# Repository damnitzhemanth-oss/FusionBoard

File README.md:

# Fusion Board

## 1. Project Overview

### What is Fusion Board ?

Fusion Board is an MPSoc (Multi-Processor System-on-Chip) built from scratch based on AMD Zynq Ultrascale + architecture.
This board features 4GB DDR4 RAM, 32GB Memory, E Ink Display and much more.
(*Note : Checkout Repo guide for repo navigation*)

### Goals and Objectives.

I designed this board to explore a new domain after making projects like [Flight controller](https://github.com/damnitzhemanth-oss/Flight_Controller/tree/main)
, [Calculator](https://github.com/damnitzhemanth-oss/Custom-Scientific-Calc).

### Key Features.

Zynq UltraScale+ XCZU4E,900-pin FBVB900 SoC with 4 GB DDR4 (4× MT40A512M16LY), 256 Mb QSPI, 32 GB eMMC, and microSD.
With High Speed connectivity Peripherals like SFP+ cage, PCIE, superspeed USB. There are 10 LDOs for different voltages such as +15V, +5V, +3V3, +2.5V, +1.8V, +0V9, +0V85.

On board barometer, GNSS, Gyro, magnetometer. With power harvester and a super capacitor for storing energy.

(*Note : There are many more amazing features, checkout [Features for Nerds](https://github.com/damnitzhemanth-oss/FusionBoard/blob/main/Guides/DetailsForNerds.md)
for detailed specs list.*)

---

## 2. Requirements

### Hardware Requirements 
(*Rough estimated prices according to LCSC, in $*)

| # | Reference | Qty | Value | LCSC Part | Subtotal (USD) |
|---:|:---|--:|:---|:---|--:|
| 1 | BT1 | 1 | Battery_Cell |  | 0.42 |
| 2 | C1,C3,C8 | 3 | 1uF |  | 0.02 |
| 3 | C2,C9,C15 | 3 | 100uF 35V |  | 0.33 |
| 4 | C4 | 1 | 100nF |  | 0.00 |
| 5 | C5,C10 | 2 | 1uF 25V |  | 0.01 |
| 6 | C6 | 1 | 2.2uF |  | 0.01 |
| 7 | C7,C26,C31,C412...C500 | 37 | 100nF |  | 0.10 |
| 8 | C11 | 1 | 0.1uF 50V X7R |  | 0.00 |
| 9 | C12,C13,C20 | 3 | 10nF 25V |  | 0.01 |
| 10 | C14,C81,C85,C111,C_shield1 | 5 | 4.7nF 50V |  | 0.01 |
| 11 | C16 | 1 | 2.2nF 25V |  | 0.00 |
| 12 | C17,C18,C66,C68,C70,C72,C74,C94,C105,C119 | 10 | 0.1uF 25V |  | 0.03 |
| 13 | C19,C21 | 2 | 0.1uF 50V |  | 0.01 |
| 14 | C22 | 1 | 47nF |  | 0.00 |
| 15 | C23,C24,C28,C29,C30,C50,C52,C60,C61,C64,C65 | 11 | 22uF |  | 0.31 |
| 16 | C25,C45,C48,C62,C101...C498 | 35 | 1uF |  | 0.10 |
| 17 | C27 | 1 | 4.7uF |  | 0.01 |
| 18 | C32,C33,C37 | 3 | 1uF |  | 0.02 |
| 19 | C34 | 1 | 0.47uF |  | 0.00 |
| 20 | C35,C39 | 2 | 10nF |  | 0.01 |
| 21 | C36,C58,C59,C63...C507 | 26 | 10uF |  | 0.29 |
| 22 | C38 | 1 | 0.1uF |  | 0.01 |
| 23 | C40 | 1 | 22uF, 6.3V |  | 0.03 |
| 24 | C41,C49 | 2 | 0.1uF, 25V |  | 0.01 |
| 25 | C42,C43,C82,C86,C103,C112,C477,C478,C495,C496 | 10 | 100pF |  | 0.03 |
| 26 | C44 | 1 | 10nF, 10V |  | 0.00 |
| 27 | C46,C79,C83,C109 | 4 | 10nF |  | 0.01 |
| 28 | C47 | 1 | 3.3nF |  | 0.00 |
| 29 | C51 | 1 | 2.2nF |  | 0.00 |
| 30 | C53,C54,C55,C56 | 4 | 47uF,4V |  | 0.22 |
| 31 | C57,C97,C99,C107,C113 | 5 | 47uF |  | 0.28 |
| 32 | C76,C78,C104 | 3 | 0.1uF 25v |  | 0.01 |
| 33 | C77,C121...C523 | 300 | 0.1uF |  | 0.83 |
| 34 | C80,C84,C91,C96,C110,C118 | 6 | 22uf 25v |  | 0.21 |
| 35 | C87,C88,C114,C481,C482 | 5 | 22pF |  | 0.01 |
| 36 | C89,C90,C92,C93,C115,C116 | 6 | 47uF 6.3V |  | 0.33 |
| 37 | C154,C174 | 2 | 47uF |  | 0.17 |
| 38 | C368,C369,C370,C380,C381,C382,C383,C392,C422 | 9 | 1nF |  | 0.03 |
| 39 | C372,C373,C408,C409 | 4 | 33pF |  | 0.01 |
| 40 | C375,C385 | 2 | 22uF |  | 0.03 |
| 41 | C424,C429,C431 | 3 | 10uF |  | 0.06 |
| 42 | C473 | 1 | 0.56 nF |  | 0.00 |
| 43 | C474 | 1 | 330 nF |  | 0.00 |
| 44 | C475 | 1 | 3.3 nF |  | 0.00 |
| 45 | C499 | 1 | 0.1 uF |  | 0.00 |
| 46 | C518 | 1 | 22F 5.5V |  | 1.11 |
| 47 | Card1 | 1 | TF-01A | C91145 | 0.17 |
| 48 | CN1 | 1 | 1-2199230-6 | C4710843 | 1.39 |
| 49 | D1 | 1 | SMBJ20A |  | 0.08 |
| 50 | D2 | 1 | 15V |  | 0.08 |
| 51 | D3 | 1 | TP7.OSMD24CA-XC |  | 0.11 |
| 52 | D4 | 1 | LSMB24CAH |  | 0.11 |
| 53 | D5 | 1 | Red |  | 0.01 |
| 54 | D6,D9 | 2 | Green |  | 0.03 |
| 55 | D7,D8 | 2 | D_Schottky |  | 0.14 |
| 56 | D10,D11,D12 | 3 | RB521S30 |  | 0.08 |
| 57 | DC1 | 1 | PJ-102AH_C3096093 | C3096093 | 0.60 |
| 58 | FB1,FB2,FB3,FB4,FB5,FB6,FB7,FB8,FB10 | 9 | 120Ω@100MHz |  | 0.06 |
| 59 | FB9 | 1 | BLM18 |  | 0.01 |
| 60 | J1 | 1 | HR911105A_C12074 | C12074 | 1.35 |
| 61 | J2 | 1 | Conn_01x03_Pin |  | 0.14 |
| 62 | J3 | 1 | USB3_B |  | 1.11 |
| 63 | J4,J5 | 2 | Conn_01x02_Pin |  | 0.22 |
| 64 | J6 | 1 | 3.3V_I2C |  | 0.11 |
| 65 | J7,J14,J15,J16 | 4 | Conn_01x10 |  | 0.83 |
| 66 | J8 | 1 | Conn_01x09_Pin |  | 0.19 |
| 67 | J9 | 1 | Conn_Coaxial |  | 1.39 |
| 68 | J10 | 1 | Conn_02x07_Odd_Even |  | 0.28 |
| 69 | J11 | 1 | Conn_01x04_Pin |  | 0.14 |
| 70 | J12 | 1 | SFP+ |  | 2.08 |
| 71 | J13 | 1 | Conn_01x22 |  | 1.11 |
| 72 | L1,L2 | 2 | 2.2uH,5A |  | 0.42 |
| 73 | L3 | 1 | 1/2.2uH |  | 0.21 |
| 74 | L4 | 1 | 0.47uH 15A |  | 0.28 |
| 75 | L5 | 1 | 10uH 12A |  | 0.28 |
| 76 | L6,L7 | 2 | 2.2uH |  | 0.42 |
| 77 | L8,L9,L10 | 3 | 1uH |  | 0.42 |
| 78 | L11 | 1 | DLW21HN900SQ2L-CUTTAPE | C80529 | 0.14 |
| 79 | L12,L13,L14 | 3 | 220 nH |  | 0.13 |
| 80 | Q1,Q2 | 2 | IPB180P04P4L-02 | C21547650 | 2.22 |
| 81 | R1,R3,R135,R138,R163,R164 | 6 | 5.1kΩ |  | 0.01 |
| 82 | R2,R13,R41,R49,R50,R52,R54,R56,R59,R153,R155,R165,R166 | 13 | 100kΩ |  | 0.02 |
| 83 | R4,R7,R20,R21,R22,R23,R24,R29,R75 | 9 | 10k |  | 0.01 |
| 84 | R5 | 1 | 100Ω |  | 0.00 |
| 85 | R6,R8,R177,R178,R181 | 5 | 4.7kΩ |  | 0.01 |
| 86 | R9,R25 | 2 | 124k |  | 0.00 |
| 87 | R10,R27,R34...R212 | 54 | 10kΩ |  | 0.08 |
| 88 | R11,R12,R60,R65,R70,R73,R74,R76,R78,R90,R101 | 11 | 100k |  | 0.02 |
| 89 | R14 | 1 | 549Ω |  | 0.00 |
| 90 | R15,R26 | 2 | 750Ω |  | 0.00 |
| 91 | R16,R17 | 2 | 470R |  | 0.00 |
| 92 | R18 | 1 | 29.8k |  | 0.00 |
| 93 | R19,R92 | 2 | 120k |  | 0.00 |
| 94 | R28 | 1 | 5.9kΩ |  | 0.00 |
| 95 | R30 | 1 | 442k |  | 0.00 |
| 96 | R31 | 1 | 210k |  | 0.00 |
| 97 | R32 | 1 | 20.5k |  | 0.00 |
| 98 | R33 | 1 | 10mΩ |  | 0.69 |
| 99 | R37,R48,R104,R105,R140,R145 | 6 | 1kΩ |  | 0.01 |
| 100 | R38 | 1 | 1k |  | 0.00 |
| 101 | R39 | 1 | 100 |  | 0.00 |
| 102 | R40 | 1 | 180Ω |  | 0.00 |
| 103 | R42 | 1 | 30.1kΩ |  | 0.00 |
| 104 | R45 | 1 | 5.23kΩ |  | 0.00 |
| 105 | R55 | 1 | 31.6K |  | 0.00 |
| 106 | R58 | 1 | 60.4k |  | 0.00 |
| 107 | R63 | 1 | 49.9k |  | 0.00 |
| 108 | R64 | 1 | 24.3kΩ |  | 0.00 |
| 109 | R67,R183,R187 | 3 | 10Ω |  | 0.00 |
| 110 | R69 | 1 | 73.2kΩ |  | 0.00 |
| 111 | R71 | 1 | 249kΩ |  | 0.00 |
| 112 | R72 | 1 | 309k |  | 0.00 |
| 113 | R77 | 1 | 200k |  | 0.00 |
| 114 | R81,R82 | 2 | 49.9kΩ |  | 0.00 |
| 115 | R85,R87,R99 | 3 | 20k |  | 0.00 |
| 116 | R86,R89,R100 | 3 | 50K |  | 0.00 |
| 117 | R88 | 1 | 182kΩ |  | 0.00 |
| 118 | R91,R93,R102 | 3 | 249k |  | 0.00 |
| 119 | R94 | 1 | 3.24kΩ |  | 0.00 |
| 120 | R95 | 1 | 14.7kΩ |  | 0.00 |
| 121 | R103 | 1 | 220Ω |  | 0.00 |
| 122 | R106,R107,R108,R109 | 4 | 240Ω |  | 0.01 |
| 123 | R110,R112,R122,R125...R139 | 11 | 22Ω |  | 0.02 |
| 124 | R124 | 1 | 11kΩ |  | 0.00 |
| 125 | R129,R132 | 2 | 470Ω |  | 0.00 |
| 126 | R137 | 1 | 8.06kΩ |  | 0.00 |
| 127 | R142,R144 | 2 | 2.49kΩ |  | 0.00 |
| 128 | R146 | 1 | 47.5kΩ |  | 0.00 |
| 129 | R147 | 1 | 22.1kΩ |  | 0.00 |
| 130 | R148,R167,R176,R209,R210 | 5 | 1MΩ |  | 0.01 |
| 131 | R149,R150,R152,R156,R157,R159,R160,R199,R200 | 9 | 2.2kΩ |  | 0.01 |
| 132 | R154 | 1 | 200kΩ |  | 0.00 |
| 133 | R161 | 1 | 12kΩ |  | 0.00 |
| 134 | R168,R175,R186,R192,R193,R195 | 6 | 50Ω |  | 0.01 |
| 135 | R169,R171 | 2 | 33Ω |  | 0.00 |
| 136 | R182,R184,R185 | 3 | 27Ω |  | 0.00 |
| 137 | R191 | 1 | 1.92kΩ |  | 0.00 |
| 138 | R196,R197,R201,R202,R203,R204,R205,R206 | 8 | 5kΩ |  | 0.01 |
| 139 | R208 | 1 | 4.02MΩ |  | 0.00 |
| 140 | R211 | 1 | 3MΩ |  | 0.00 |
| 141 | RT1 | 1 | 10k NTC |  | 0.04 |
| 142 | R_shield1 | 1 | 1 M |  | 0.00 |
| 143 | SW1 | 1 | SW_Push |  | 0.21 |
| 144 | SW2 | 1 | SW_SPDT |  | 0.28 |
| 145 | TP1,TP2 | 2 | TestPoint |  | 0.14 |
| 146 | U1 | 1 | TPD6S300ARUKR | C2876380 | 0.51 |
| 147 | U2 | 1 | STUSB4500QTR |  | 2.08 |
| 148 | U3 | 1 | TVS2201DRBR | C1849889 | 0.21 |
| 149 | U4,U6 | 2 | TPS259470ARPWR | C3662799 | 10.34 |
| 150 | U5 | 1 | TPS2121RUXR | C485916 | 0.53 |
| 151 | U7 | 1 | XT60 | C98733 | 0.28 |
| 152 | U8 | 1 | DW06 | C917080 | 0.07 |
| 153 | U9 | 1 | BQ25895RTWR | C80200 | 2.17 |
| 154 | U10 | 1 | BQ27441DRZR-G1A | C473397 | 1.41 |
| 155 | U11 | 1 | LM66100DCK |  | 0.42 |
| 156 | U12 | 1 | TPS61088RHLR | C87357 | 0.67 |
| 157 | U13 | 1 | TPS548A20RVER | C468255 | 1.08 |
| 158 | U14 | 1 | TPS62130RGTR | C43590 | 0.92 |
| 159 | U15,U20,U21,U25 | 4 | TPS54824RNVR | C2070614 | 4.32 |
| 160 | U16 | 1 | TPS62823DLCR | C2693497 | 0.32 |
| 161 | U17 | 1 | TPS62822DLCR | C473385 | 0.20 |
| 162 | U18,U22,U23,U26 | 4 | TPS7A4700RGWR | C114839 | 9.32 |
| 163 | U19 | 1 | TPS3700DSET | C2869244 | 0.56 |
| 164 | U24 | 1 | RS3112-1.25XSF3 | C19269195 | 0.11 |
| 165 | U27 | 1 | xczu4evfbvb900pkg |  | 3000.00 |
| 166 | U28 | 1 | TXS02612RTWR | C140276 | 1.52 |
| 167 | U29 | 1 | MT25QU256ABA8ESF-0SIT TR | C2061781 | 20.23 |
| 168 | U30 | 1 | FEMDNN032G-A3A55 | C5117593 | 37.90 |
| 169 | U31 | 1 | DP83867IRRGZR | C2678038 | 2.09 |
| 170 | U32 | 1 | CP2102N-A02-GQFN24 |  | 1.39 |
| 171 | U33 | 1 | USB3320C-EZK-TR | C132156 | 1.49 |
| 172 | U34,U39 | 2 | TPD4E05U06DQA |  | 0.83 |
| 173 | U35,U53 | 2 | TCA9548APWR |  | 2.78 |
| 174 | U36 | 1 | TXB0108PW |  | 1.11 |
| 175 | U37 | 1 | PCA9306 |  | 0.42 |
| 176 | U38 | 1 | USB2514B_Bi |  | 2.08 |
| 177 | U40 | 1 | TXS0102DQE |  | 0.42 |
| 178 | U41 | 1 | SI5341A-D12636-GM | C3609093 | 20.28 |
| 179 | U42 | 1 | REF5025AD |  | 3.47 |
| 180 | U43 | 1 | LMX2594RHAR | C2862572 | 68.58 |
| 181 | U44 | 1 | ADS131M08IPBS | C2685451 | 6.76 |
| 182 | U45 | 1 | ADS4245IRGCT | C2670075 | 59.37 |
| 183 | U46 | 1 | AD9744ARUZRL7 | C461519 | 11.48 |
| 184 | U47 | 1 | THS4509RGTT | C2057531 | 6.27 |
| 185 | U48 | 1 | ADL8100ACPZN |  | 11.11 |
| 186 | U49 | 1 | BPF-A355 |  | 20.83 |
| 187 | U50 | 1 | TMP117DRVR |  | 2.08 |
| 188 | U51 | 1 | ICM-42688-P |  | 2.78 |
| 189 | U52 | 1 | MMC5983MA | C404329 | 3.43 |
| 190 | U54 | 1 | BMP581 | C5362283 | 1.67 |
| 191 | U55 | 1 | MAX-M10S-00B | C4153167 | 10.42 |
| 192 | U56 | 1 | ATECC608B-MAHDA |  | 1.11 |
| 193 | U57 | 1 | OPTIGA TPM SLB 9673 FW26 |  | 3.47 |
| 194 | U58 | 1 | BQ25570 |  | 3.47 |
| 195 | U59 | 1 | STM32G0B1RBT6 |  | 2.08 |
| 196 | USB1,USB2,USB3 | 3 | TYPE-C-24P-SMD | C53207146 | 0.50 |
| 197 | USB4 | 1 | 472720001 | C587824 | 1.25 |
| 198 | U_RAM1,U_RAM2,U_RAM3,U_RAM4 | 4 | MT40A512M16LY-075:E | C598779 | 13.89 |
| 199 | Y1,Y2,Y7 | 3 | 25 MHz |  | 0.63 |
| 200 | Y3 | 1 | 26 MHz |  | 0.21 |
| 201 | Y4 | 1 | SiT9365AI-4B2-33E100.0000000 |  | 4.17 |
| 202 | Y5 | 1 | ECS_480-8-37-A-D-P-TR |  | 0.28 |
| 203 | Y6 | 1 | SiT5356AI-FP-25VT-16.367667 |  | 6.94 |
|  | **TOTAL** |  |  |  | **≈ 3,747.37** |

### Software and Tools.

To flash this board you would need tools like Vivado and vitis. STSW-STUSB002 for PD Control. 

### Constraints and Challenges.

This is not a simple hobbyist project. This is an 16 layer board with numerous constraints. As a 14 year old with not much experience this board might not be stable. And I cannot manufacture it, as total cost is more than 3000$.

---

## 3. Development Logs.

### Daily Logs.

Check [Journal](https://github.com/damnitzhemanth-oss/FusionBoard/blob/main/Guides/journal.md) for day to day feats, challenges and much more.

## 4. PCB 

### Schematic 

Entire schematic is divided into 12 sheets. Each sheet serves a different purpose. Zynq section is further divided into 4 sheets. Checkout [Schematics Folder](https://github.com/damnitzhemanth-oss/FusionBoard/tree/main/Images/Schematics) for more images.

### PCB

16 layers. No DRC errors. 

## 5. Repo Architecture 

Checkout [RepoNav](https://github.com/damnitzhemanth-oss/FusionBoard/blob/dbc74cef5dea421e17314afc9f19d36bd8f9f652/Guides/RepoNav.md)

## 6.Gallery 

### PCB

## 7.Credits 

- [KiCad](https://www.google.com/url?opi=89978449&q=https://www.kicad.org/&sa=U&ved=2ahUKEwimlZP32eWXAxW-jOEIHdIBCzUQFnoECBEQAQ&usg=AOvVaw3RWTRyOBHwgJWf9Tp2GrV8), used as cad.
- [KiPart](https://pypi.org/project/kipart/) python package for symbol creation.
- [easyeda2kicad](https://github.com/BiggiePete/easyeda2kicad-App) extension for downloading footprint,symbols, 3d models.
- Interactive BOM Plugin.
- Round Corners Plugin.
- Notable Mentions : Ultra librarian, Component Search Engine and my music playlist.

## 8. AI Usage 
I used AI for verifying connections and clear my doubts only in first 4 sessions. After that I didn't use AI for anything. Checkout [Journal](https://github.com/damnitzhemanth-oss/FusionBoard/blob/main/Guides/journal.md) for day to day AI usage.

## 9. CAD

No cad, check CAD folder for KiCad exported cad File.

## 10. License.

MIT License. You are free to use this, modify this, experiment with this. But no accountability for failure will be taken. Credits are appreciated.

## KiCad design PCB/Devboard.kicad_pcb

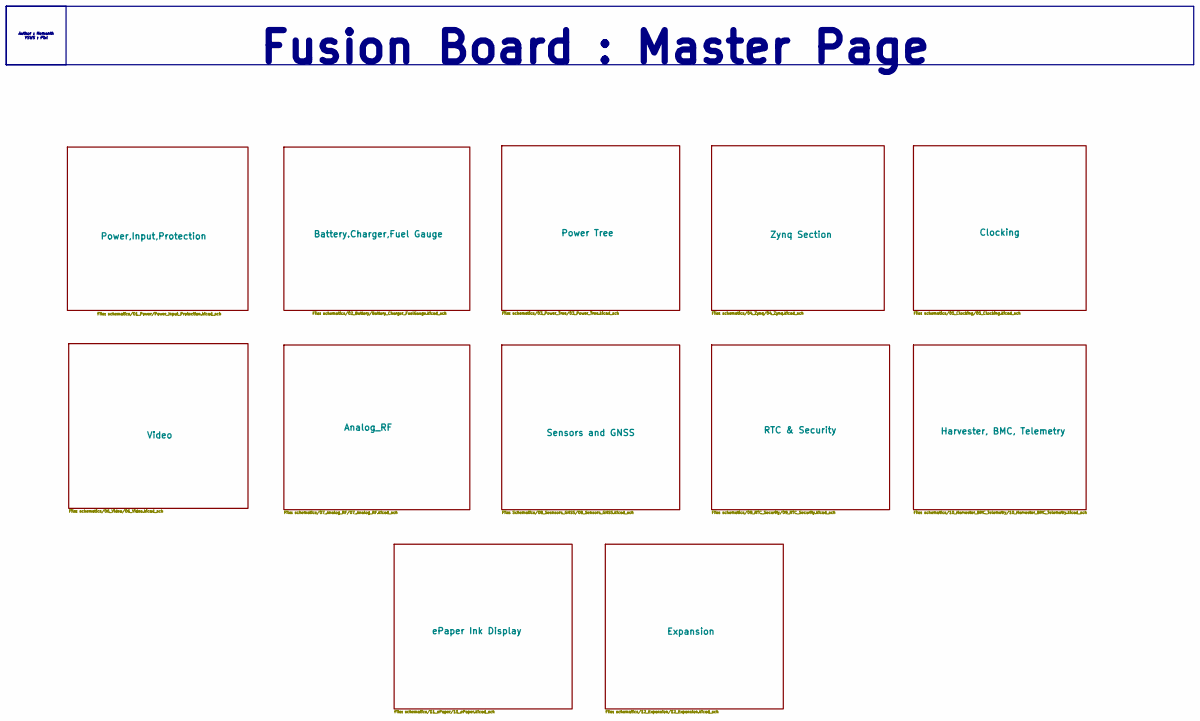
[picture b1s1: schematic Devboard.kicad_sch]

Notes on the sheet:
Fusion Board : Master Page
Author : Hemanth YSWS : Pixl

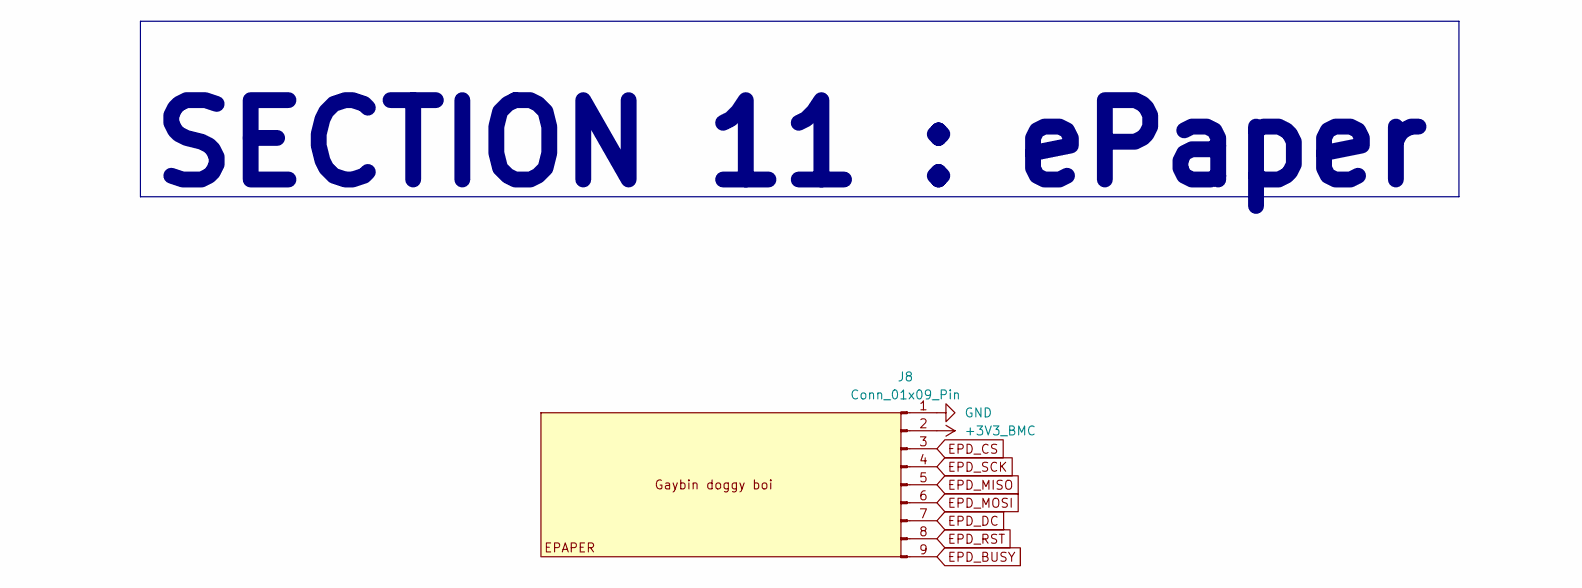
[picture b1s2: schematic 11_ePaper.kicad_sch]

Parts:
J8: Conn_01x09_Pin; PinHeader_1x09_P2.54mm_Vertical

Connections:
+3V3_BMC: J8.2; also elsewhere on the board
EPD_BUSY: J8.9; also elsewhere on the board
EPD_CS: J8.3; also elsewhere on the board
EPD_DC: J8.7; also elsewhere on the board
EPD_MISO: J8.5; also elsewhere on the board
EPD_MOSI: J8.6; also elsewhere on the board
EPD_RST: J8.8; also elsewhere on the board
EPD_SCK: J8.4; also elsewhere on the board
GND: J8.1; also elsewhere on the board

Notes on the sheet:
SECTION 11 : ePaper

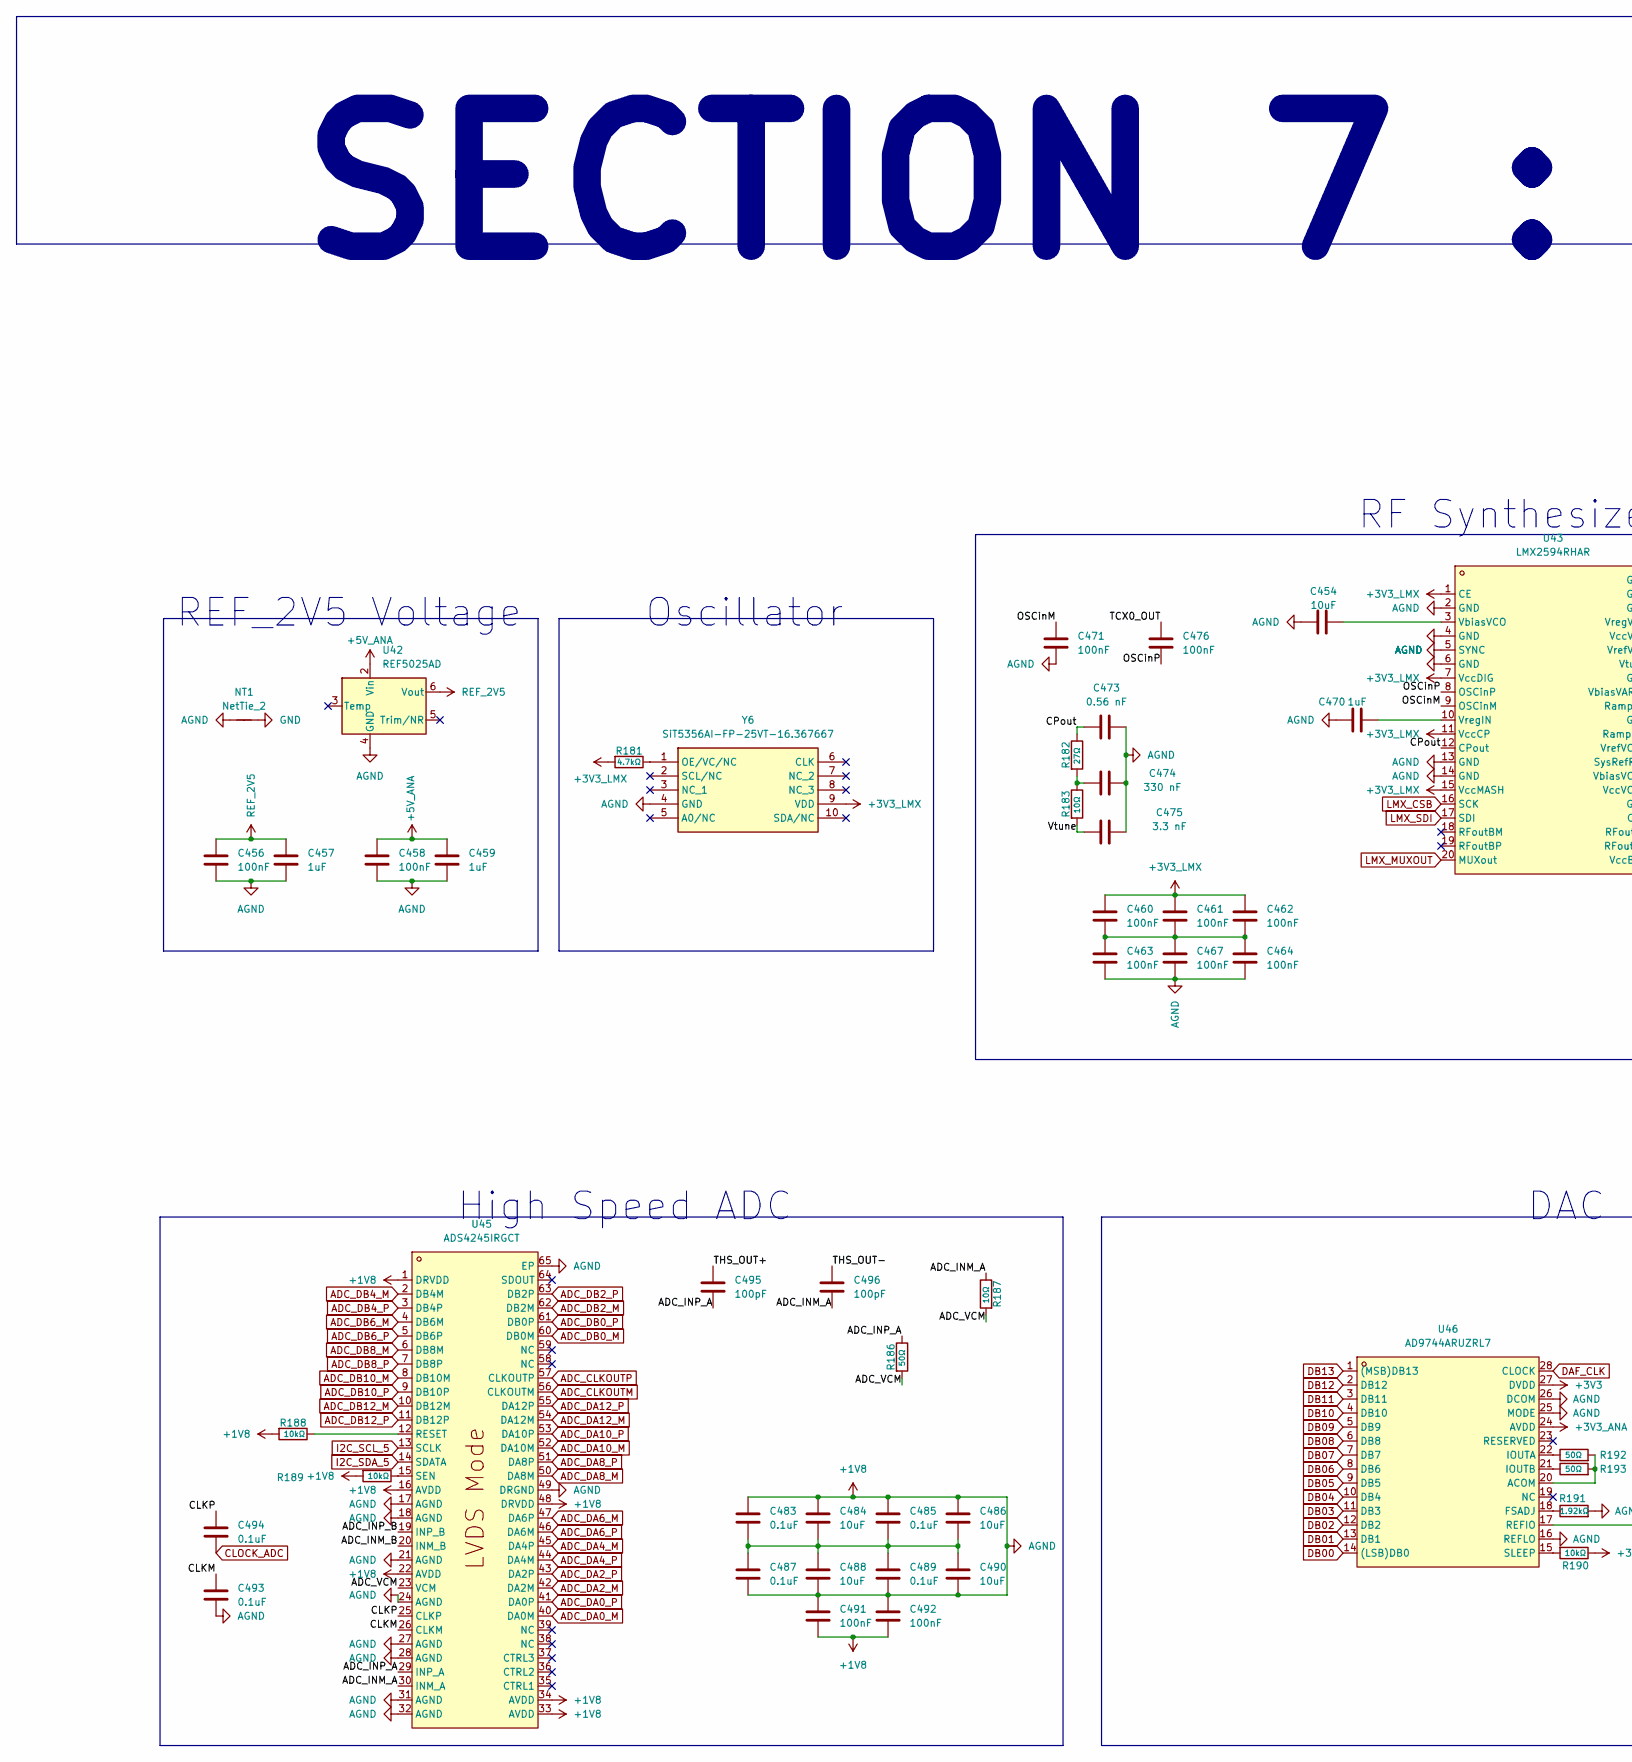
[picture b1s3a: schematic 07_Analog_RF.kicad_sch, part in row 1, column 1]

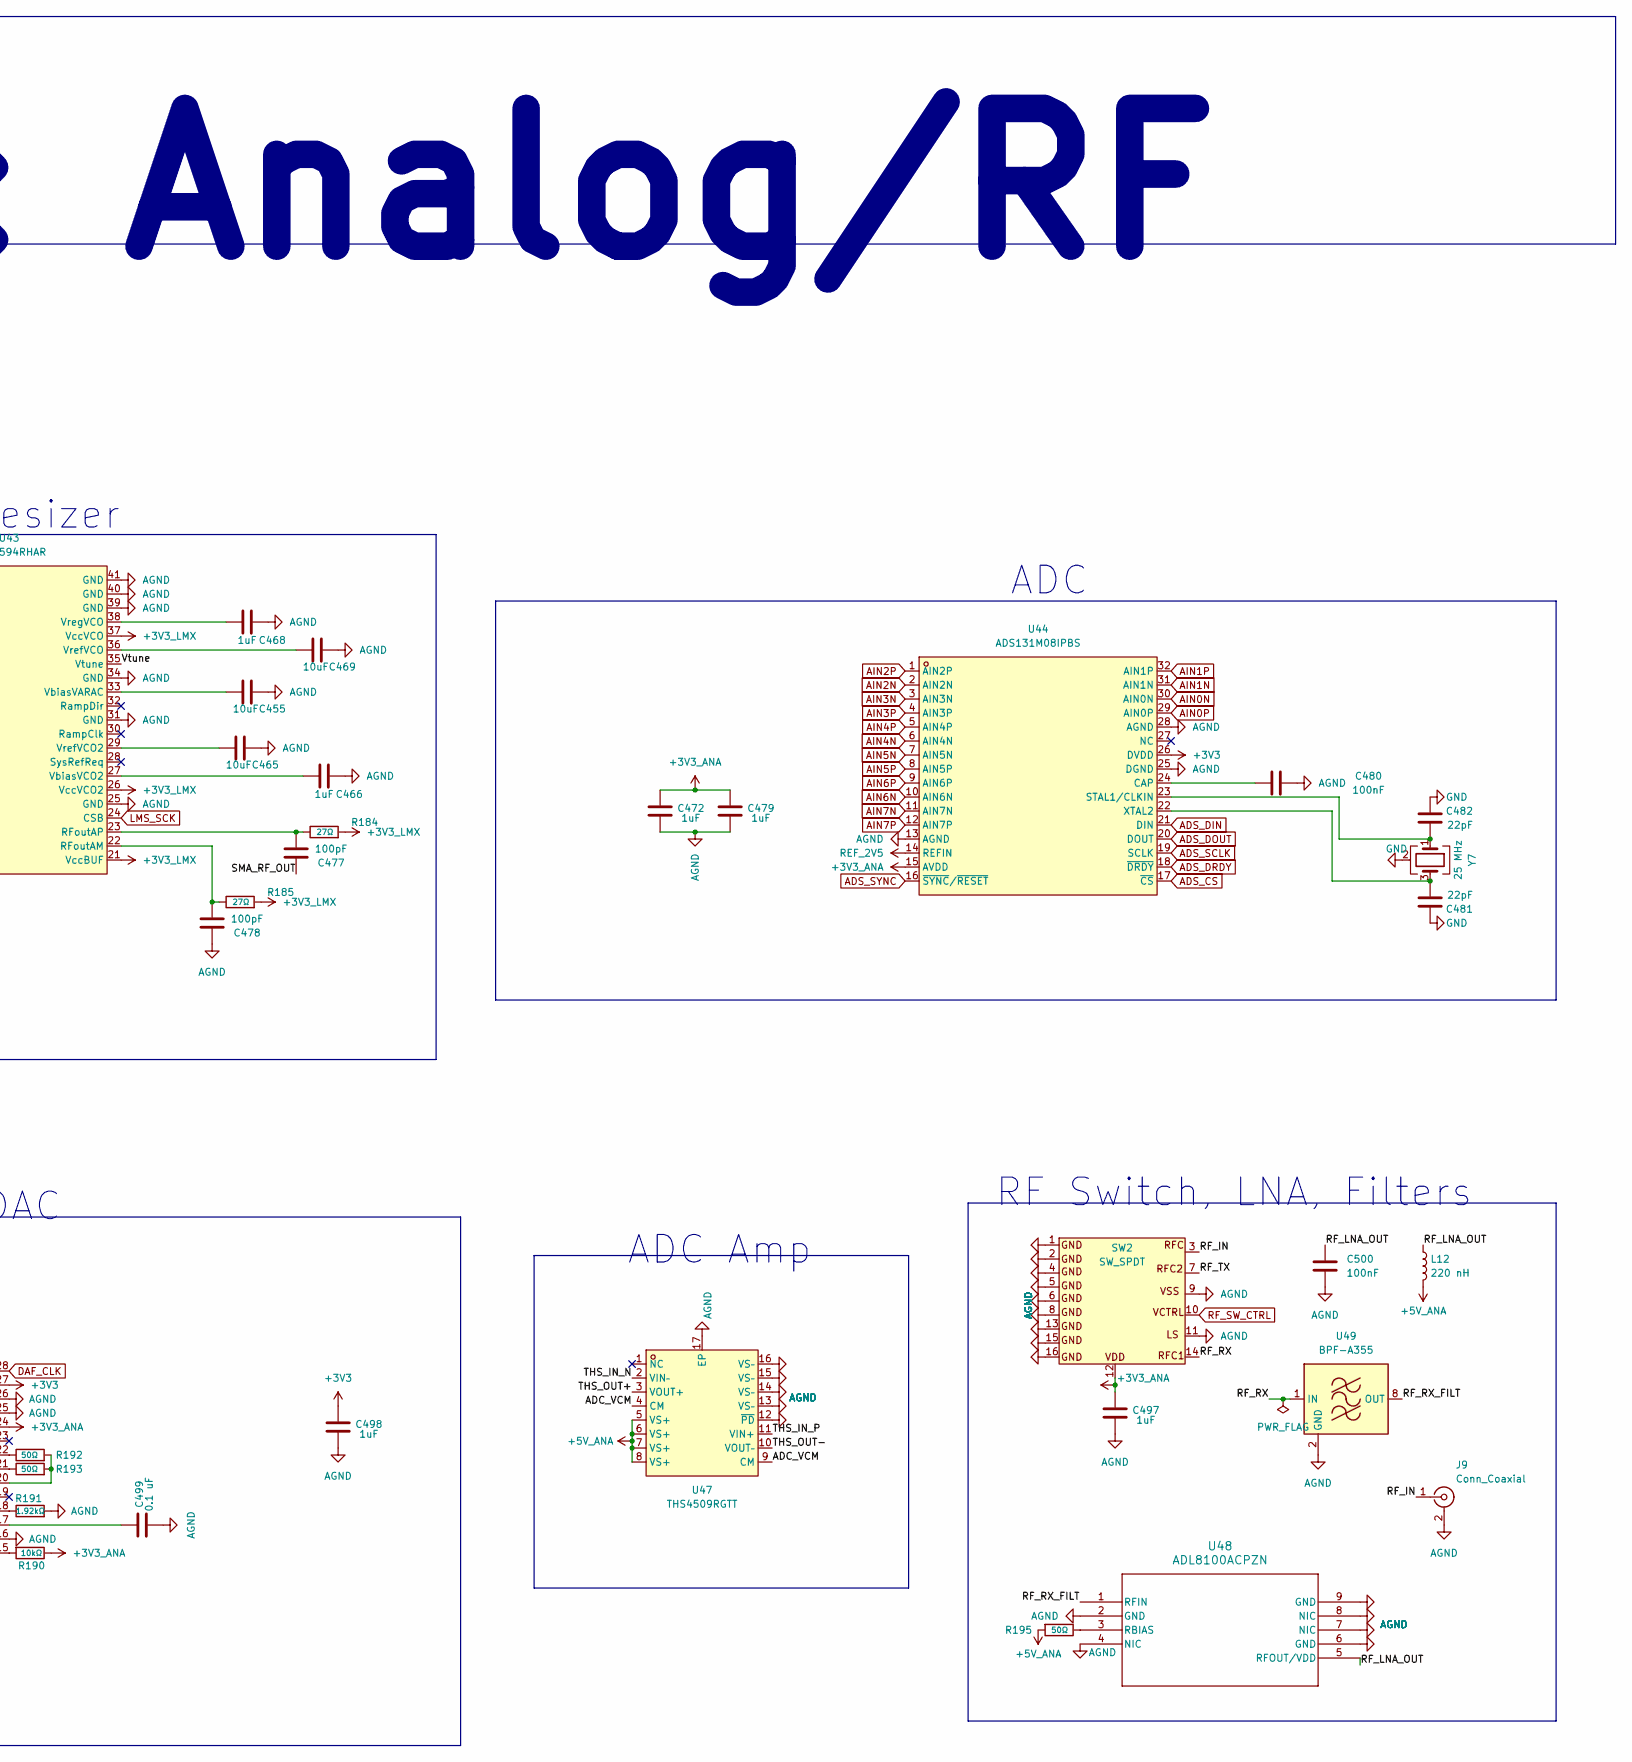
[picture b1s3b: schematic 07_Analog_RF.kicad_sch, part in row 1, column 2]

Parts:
C454, C455, C465, C469, C484, C486, C488, C490: 10uF; C_0402_1005Metric
C456, C458, C460, C461, C462, C463, C464, C467, C471, C476, C480, C491, C492, C500: 100nF; C_0402_1005Metric
C457, C459, C466, C468, C470, C472, C479, C497, C498: 1uF; C_0402_1005Metric
C473: 0.56 nF; C_0402_1005Metric
C474: 330 nF; C_0402_1005Metric
C475: 3.3 nF; C_0402_1005Metric
C477, C478, C495, C496: 100pF; C_0402_1005Metric
C481, C482: 22pF; C_0402_1005Metric
C483, C485, C487, C489, C493, C494: 0.1uF; C_0402_1005Metric
C499: 0.1 uF; C_0402_1005Metric
J9: Conn_Coaxial; SMA_Amphenol_132289_EdgeMount
L12: 220 nH; L_0603_1608Metric
NT1: NetTie_2; NetTie-2_SMD_Pad0.5mm
R181: 4.7kΩ; R_0402_1005Metric
R182, R184, R185: 27Ω; R_0402_1005Metric
R183, R187: 10Ω; R_0402_1005Metric
R186, R192, R193, R195: 50Ω; R_0402_1005Metric
R188, R189, R190: 10kΩ; R_0402_1005Metric
R191: 1.92kΩ; R_0402_1005Metric
SW2: SW_SPDT; LFCSP-16-1EP_3x3mm_P0.5mm_EP1.6x1.6mm
U42: REF5025AD; SOIC-8_3.9x4.9mm_P1.27mm
U43: LMX2594RHAR; QFN-40_L6.0-W6.0-P0.50-BL-EP4.5; MPN LMX2594RHAR; LCSC Part C2862572
U44: ADS131M08IPBS; TQFP-32_L5.0-W5.0-P0.50-LS7.0-TL; MPN ADS131M08IPBS; LCSC Part C2685451
U45: ADS4245IRGCT; VQFN-64_L9.0-W9.0-P0.50-TL-EP7.4; MPN ADS4245IRGCT; LCSC Part C2670075
U46: AD9744ARUZRL7; TSSOP-28_L9.7-W4.4-P0.65-LS6.4-BL; MPN AD9744ARUZRL7; LCSC Part C461519
U47: THS4509RGTT; VQFN-16_L3.0-W3.0-P0.50-TL-EP1.5; MPN THS4509RGTT; LCSC Part C2057531
U48: ADL8100ACPZN; CP-8-30_ADI
U49: BPF-A355; Mini-Circuits_HQ1157
Y6: SiT5356AI-FP-25VT-16.367667; Ceramic_QFN_5032_10pins; Manufacturer_Part_Number SiT5356AI-FP-25VT-16.367667
Y7: 25 MHz; Crystal_SMD_3225-4Pin_3.2x2.5mm

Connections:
+1V8: C454.1, C455.1, C456.1, C457.1, C458.1, C459.1, C463.1, C464.1, C465.1, C466.1, C467.1, C468.1, C469.1, C470.1, C471.1, C472.1, C473.1, C474.1, C475.1, C478.2, C479.1, C480.1, C483.1, C484.2, C485.1, C486.2, C487.2, C488.1, C489.2, C490.1, C491.1, C491.2, C492.1, C492.2, C493.2, C497.1, C498.1, C499.1, C500.2, J9.2 (Ext), NT1.1, R188.2, R189.2, R191.2, SW2.1 (GND), SW2.2 (GND), SW2.4 (GND), SW2.5 (GND), SW2.6 (GND), SW2.8 (GND), SW2.9 (VSS), SW2.11 (LS), SW2.13 (GND), SW2.15 (GND), SW2.16 (GND), U42.4 (GND), U43.2 (GND), U43.4 (GND), U43.5 (SYNC), U43.6 (GND), U43.13 (GND), U43.14 (GND), U43.25 (GND), U43.31 (GND), U43.34 (GND), U43.39 (GND), U43.40 (GND), U43.41 (GND), U44.13 (AGND), U44.25 (DGND), U44.28 (AGND), U45.1 (DRVDD), U45.16 (AVDD), U45.17 (AGND), U45.18 (AGND), U45.21 (AGND), U45.22 (AVDD), U45.24 (AGND), U45.27 (AGND), U45.28 (AGND), U45.31 (AGND), U45.32 (AGND), U45.33 (AVDD), U45.34 (AVDD), U45.48 (DRVDD), U45.49 (DRGND), U45.65 (EP), U46.16 (REFLO), U46.25 (MODE), U46.26 (DCOM), U47.12 (~PD), U47.13 (VS–), U47.14 (VS–), U47.15 (VS–), U47.16 (VS–), U47.17 (EP), U48.2 (GND), U48.4 (NIC), U48.6 (GND), U48.7 (NIC), U48.8 (NIC), U48.9 (GND), U49.2 (GND), U49.3 (GND), U49.4 (GND), U49.5 (GND), U49.6 (GND), U49.7 (GND), U49.9 (GND), U49.10 (GND), U49.11 (GND), U49.12 (GND), U49.13 (GND), U49.14 (GND), Y6.4 (GND); also elsewhere on the board
+3V3: C498.2, U44.26 (DVDD), U46.27 (DVDD); also elsewhere on the board
+3V3_ANA: C472.2, C479.2, C497.2, R190.1, SW2.12 (VDD), U44.15 (AVDD), U46.24 (AVDD); also elsewhere on the board
+3V3_LMX: C460.2, C461.2, C462.2, R181.2, R184.2, R185.2, U43.1 (CE), U43.7 (VccDIG), U43.11 (VccCP), U43.15 (VccMASH), U43.21 (VccBUF), U43.26 (VccVCO2), U43.37 (VccVCO), Y6.9 (VDD); also elsewhere on the board
+5V_ANA: C458.2, C459.2, L12.2, R195.2, U42.2 (Vin), U47.5 (VS+), U47.6 (VS+), U47.7 (VS+), U47.8 (VS+); also elsewhere on the board
/Analog_RF/ADC_INM_A: C496.2, R187.1, U45.30 (INM_A)
/Analog_RF/ADC_INM_B: U45.20 (INM_B)
/Analog_RF/ADC_INP_A: C495.2, R186.1, U45.29 (INP_A)
/Analog_RF/ADC_INP_B: U45.19 (INP_B)
/Analog_RF/ADC_VCM: R186.2, R187.2, U45.23 (VCM), U47.4 (CM), U47.9 (CM)
/Analog_RF/CLKM: C493.1, U45.26 (CLKM)
/Analog_RF/CLKP: C494.1, U45.25 (CLKP)
/Analog_RF/CPout: C473.2, R182.1, U43.12 (CPout)
/Analog_RF/OSCinM: C471.2, U43.9 (OSCinM)
/Analog_RF/OSCinP: C476.1, U43.8 (OSCinP)
/Analog_RF/RF_IN: J9.1 (In), SW2.3 (RFC)
/Analog_RF/RF_LNA_OUT: C500.1, L12.1, U48.5 (RFOUT/VDD)
/Analog_RF/RF_RX: SW2.14 (RF2), U49.1 (IN)
/Analog_RF/RF_RX_FILT: U48.1 (RFIN), U49.8 (OUT)
/Analog_RF/RF_TX: SW2.7 (RF2)
/Analog_RF/SMA_RF_OUT: C477.2
/Analog_RF/TCX0_OUT: C476.2
/Analog_RF/THS_IN_N: U47.2 (VIN–)
/Analog_RF/THS_IN_P: U47.11 (VIN+)
/Analog_RF/THS_OUT+: C495.1, U47.3 (VOUT+)
/Analog_RF/THS_OUT-: C496.1, U47.10 (VOUT–)
/Analog_RF/Vtune: C475.2, R183.2, U43.35 (Vtune)
ADC_CLKOUTM: U45.56 (CLKOUTM); also elsewhere on the board
ADC_CLKOUTP: U45.57 (CLKOUTP); also elsewhere on the board
ADC_DA0_M: U45.40 (DA0M); also elsewhere on the board
ADC_DA0_P: U45.41 (DA0P); also elsewhere on the board
ADC_DA2_M: U45.42 (DA2M); also elsewhere on the board
ADC_DA2_P: U45.43 (DA2P); also elsewhere on the board
ADC_DA4_M: U45.45 (DA4P); also elsewhere on the board
ADC_DA4_P: U45.44 (DA4M); also elsewhere on the board
ADC_DA6_M: U45.47 (DA6P); also elsewhere on the board
ADC_DA6_P: U45.46 (DA6M); also elsewhere on the board
ADC_DA8_M: U45.50 (DA8M); also elsewhere on the board
ADC_DA8_P: U45.51 (DA8P); also elsewhere on the board
ADC_DA10_M: U45.52 (DA10M); also elsewhere on the board
ADC_DA10_P: U45.53 (DA10P); also elsewhere on the board
ADC_DA12_M: U45.54 (DA12M); also elsewhere on the board
ADC_DA12_P: U45.55 (DA12P); also elsewhere on the board
ADC_DB0_M: U45.60 (DB0M); also elsewhere on the board
ADC_DB0_P: U45.61 (DB0P); also elsewhere on the board
ADC_DB2_M: U45.62 (DB2M); also elsewhere on the board
ADC_DB2_P: U45.63 (DB2P); also elsewhere on the board
ADC_DB4_M: U45.2 (DB4M); also elsewhere on the board
ADC_DB4_P: U45.3 (DB4P); also elsewhere on the board
ADC_DB6_M: U45.4 (DB6M); also elsewhere on the board
ADC_DB6_P: U45.5 (DB6P); also elsewhere on the board
ADC_DB8_M: U45.6 (DB8M); also elsewhere on the board
ADC_DB8_P: U45.7 (DB8P); also elsewhere on the board
ADC_DB10_M: U45.8 (DB10M); also elsewhere on the board
ADC_DB10_P: U45.9 (DB10P); also elsewhere on the board
ADC_DB12_M: U45.10 (DB12M); also elsewhere on the board
ADC_DB12_P: U45.11 (DB12P); also elsewhere on the board
ADS_CS: U44.17 (~CS); also elsewhere on the board
ADS_DIN: U44.21 (DIN); also elsewhere on the board
ADS_DOUT: U44.20 (DOUT); also elsewhere on the board
ADS_DRDY: U44.18 (~DRDY); also elsewhere on the board
ADS_SCLK: U44.19 (SCLK); also elsewhere on the board
ADS_SYNC: U44.16 (~SYNC/~RESET); also elsewhere on the board
AIN0N: U44.30 (AIN0N)
AIN0P: U44.29 (AIN0P)
AIN1N: U44.31 (AIN1N)
AIN1P: U44.32 (AIN1P)
AIN2N: U44.2 (AIN2N)
AIN2P: U44.1 (AIN2P)
AIN3N: U44.3 (AIN3N)
AIN3P: U44.4 (AIN3P)
AIN4N: U44.6 (AIN4N)
AIN4P: U44.5 (AIN4P)
AIN5N: U44.7 (AIN5N)
AIN5P: U44.8 (AIN5P)
AIN6N: U44.10 (AIN6N)
AIN6P: U44.9 (AIN6P)
AIN7N: U44.11 (AIN7N)
AIN7P: U44.12 (AIN7P)
CLOCK_ADC: C494.2; also elsewhere on the board
DAF_CLK: U46.28 (CLOCK); also elsewhere on the board
DB00: U46.14 ((LSB)DB0)
DB01: U46.13 (DB1)
DB02: U46.12 (DB2)
DB03: U46.11 (DB3)
DB04: U46.10 (DB4)
DB05: U46.9 (DB5)
DB06: U46.8 (DB6)
DB07: U46.7 (DB7)
DB08: U46.6 (DB8)
DB09: U46.5 (DB9)
DB10: U46.4 (DB10)
DB11: U46.3 (DB11)
DB12: U46.2 (DB12)
DB13: U46.1 ((MSB)DB13)
GND: C481.1, C482.1, NT1.2, Y7.2 (G), Y7.4 (G); also elsewhere on the board
I2C_SCL_5: U45.13 (SCLK); also elsewhere on the board
I2C_SDA_5: U45.14 (SDATA); also elsewhere on the board
LMS_SCK: U43.24 (CSB); also elsewhere on the board
LMX_CSB: U43.16 (SCK); also elsewhere on the board
LMX_MUXOUT: U43.20 (MUXout); also elsewhere on the board
LMX_SDI: U43.17 (SDI); also elsewhere on the board
unnamed: C460.1, C461.1, C462.1, C463.2, C464.2, C467.2
unnamed: C474.2, R182.2, R183.1
unnamed: C483.2, C484.1, C485.2, C486.1, C487.1, C488.2, C489.1, C490.2
unnamed: C478.1, R185.1, U43.22 (RFoutAM)
unnamed: C477.1, R184.1, U43.23 (RFoutAP)
unnamed: C455.2, U43.33 (VbiasVARAC)
unnamed: C466.2, U43.27 (VbiasVCO2)
unnamed: C454.2, U43.3 (VbiasVCO)
unnamed: C465.2, U43.29 (VrefVCO2)
unnamed: C469.2, U43.36 (VrefVCO)
unnamed: C470.2, U43.10 (VregIN)
unnamed: C468.2, U43.38 (VregVCO)
unnamed: C480.2, U44.24 (CAP)
unnamed: C482.2, U44.23 (STAL1/CLKIN), Y7.1
unnamed: C481.2, U44.22 (XTAL2), Y7.3
unnamed: R188.1, U45.12 (RESET)
unnamed: R189.1, U45.15 (SEN)
unnamed: R192.2, R193.2, U46.20 (ACOM)
unnamed: R191.1, U46.18 (FSADJ)
unnamed: R192.1, U46.22 (IOUTA)
unnamed: R193.1, U46.21 (IOUTB)
unnamed: C499.2, U46.17 (REFIO)
unnamed: R190.2, U46.15 (SLEEP)
unnamed: R195.1, U48.3 (RBIAS)
unnamed: R181.1, Y6.1 (OE/VC/NC)
REF_2V5: C456.2, C457.2, U42.6 (Vout), U44.14 (REFIN)
RF_SW_CTRL: SW2.10 (VCTRL)

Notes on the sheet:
ADC Amp
DAC
RF Synthesizer
REF_2V5 Voltage
High Speed ADC
RF Switch, LNA, Filters
ADC
Oscillator
SECTION 7 : Analog/RF

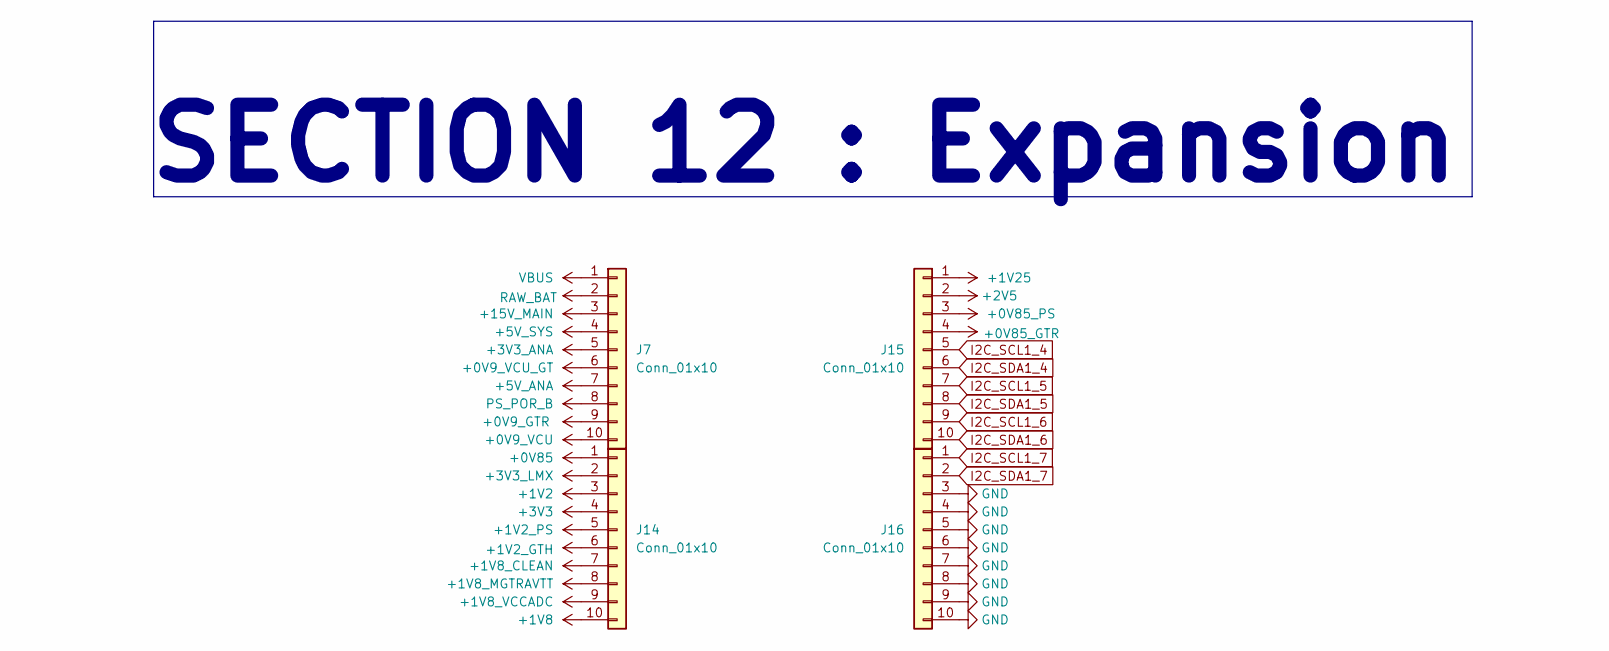
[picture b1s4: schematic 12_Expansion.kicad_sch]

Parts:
J7, J14, J15, J16: Conn_01x10; PinHeader_1x10_P2.54mm_Vertical

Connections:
+0V9_GTR: J7.9; also elsewhere on the board
+0V9_VCU: J7.10; also elsewhere on the board
+0V9_VCU_GT: J7.6; also elsewhere on the board
+0V85: J14.1; also elsewhere on the board
+0V85_GTR: J15.4; also elsewhere on the board
+0V85_PS: J15.3; also elsewhere on the board
+1V2: J14.3; also elsewhere on the board
+1V2_GTH: J14.6; also elsewhere on the board
+1V2_PS: J14.5; also elsewhere on the board
+1V8: J14.10; also elsewhere on the board
+1V8_CLEAN: J14.7; also elsewhere on the board
+1V8_MGTRAVTT: J14.8; also elsewhere on the board
+1V8_VCCADC: J14.9; also elsewhere on the board
+1V25: J15.1; also elsewhere on the board
+2V5: J15.2; also elsewhere on the board
+3V3: J14.4; also elsewhere on the board
+3V3_ANA: J7.5; also elsewhere on the board
+3V3_LMX: J14.2; also elsewhere on the board
+5V_ANA: J7.7; also elsewhere on the board
+5V_SYS: J7.4; also elsewhere on the board
+15V_MAIN: J7.3; also elsewhere on the board
GND: J16.3, J16.4, J16.5, J16.6, J16.7, J16.8, J16.9, J16.10; also elsewhere on the board
I2C_SCL1_4: J15.5; also elsewhere on the board
I2C_SCL1_5: J15.7; also elsewhere on the board
I2C_SCL1_6: J15.9; also elsewhere on the board
I2C_SCL1_7: J16.1; also elsewhere on the board
I2C_SDA1_4: J15.6; also elsewhere on the board
I2C_SDA1_5: J15.8; also elsewhere on the board
I2C_SDA1_6: J15.10; also elsewhere on the board
I2C_SDA1_7: J16.2; also elsewhere on the board
PS_POR_B: J7.8; also elsewhere on the board
RAW_BAT: J7.2; also elsewhere on the board
VBUS: J7.1; also elsewhere on the board

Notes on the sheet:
SECTION 12 : Expansion
